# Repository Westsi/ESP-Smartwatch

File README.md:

# ESP32 Based Smartwatch
A smartwatch with modern features such as notifications and Spotify sync, watch faces that can be customised, a 240x240 round LCD screen, and a companion app connected with a custom BLE profile.

## Features
- Custom BLE Profile allowing for
  - Notification Sync
  - Time Sync
  - Spotify Sync
  - Exercise Sync
- Auto Sleep Timeout to save battery
- Adjustable Brightness
- Semi-customizeable Watch Faces
- Rudimentary Exercise Tracker
- Code for wireless (OTA) updates (most code from [fbiego/ESP32_BLE_OTA_Arduino](https://github.com/fbiego/ESP32_BLE_OTA_Arduino))

## Prototype 1

[Demo Video (youtube.com)](https://www.youtube.com/watch?v=f3tLT5q3JZY)

## TODO
- [ ] Fix OTA updates over BLE
- [ ] Make weather sync as well
- [x] Put it all together
- [ ] Calibrate battery level code
- [ ] Make Exercise Tracker work properly with accelerometer
- [ ] Saveable Preferences

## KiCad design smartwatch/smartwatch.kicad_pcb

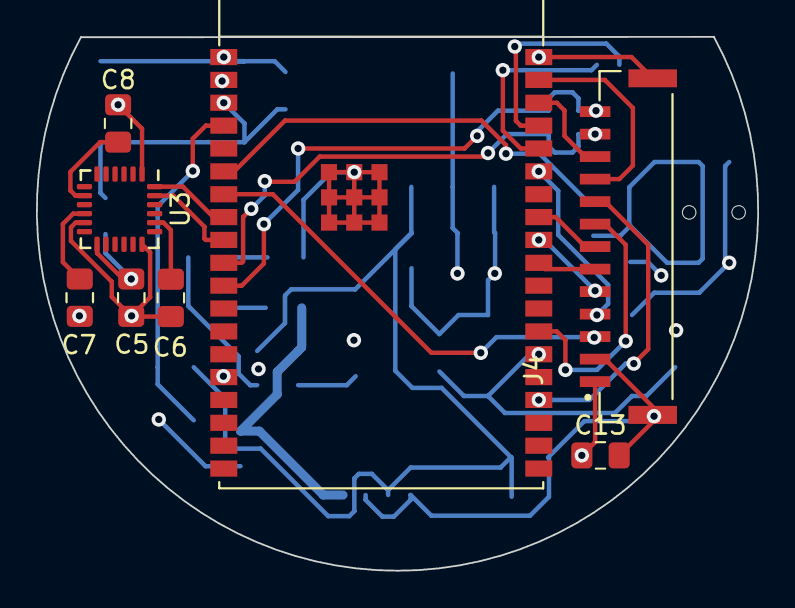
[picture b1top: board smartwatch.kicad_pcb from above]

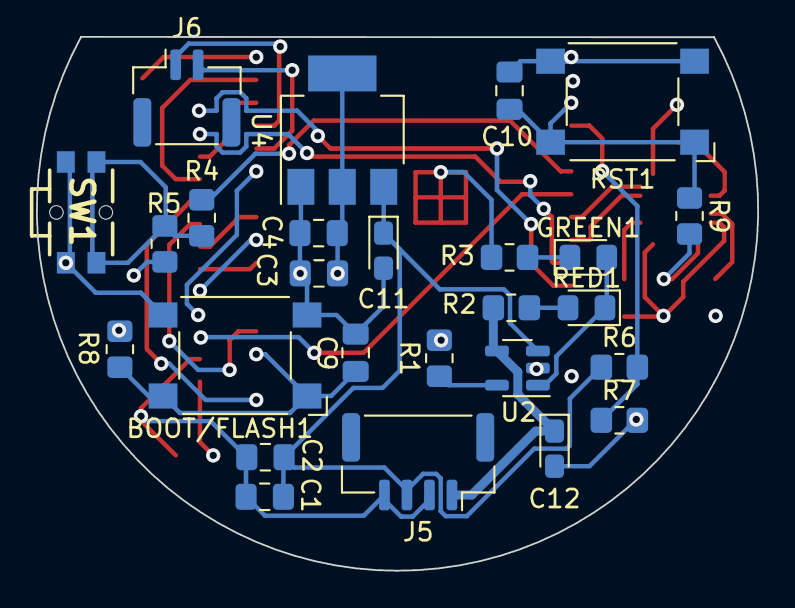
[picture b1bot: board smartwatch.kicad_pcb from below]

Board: 4 copper layers, 40.1 x 29.7 mm, 34 parts (26 on the bottom side), 31 nets.

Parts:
BOOT/FLASH1: BOOT/FLASH; SW_SPST_Omron_B3FS-100xP
C1, C4, C8, C13: 10nF; C_0805_2012Metric_Pad1.18x1.45mm_HandSolder
C2, C3, C9, C10: 100nF; C_0805_2012Metric_Pad1.18x1.45mm_HandSolder
C5, C7: 0.1uF; C_0805_2012Metric_Pad1.18x1.45mm_HandSolder
C6: 2.2nF; C_0805_2012Metric_Pad1.18x1.45mm_HandSolder
C11, C12: Polarized_10uF; CP_EIA-2012-12_Kemet-R_Pad1.30x1.05mm_HandSolder
GREEN1: CHARGED; LED_0805_2012Metric_Pad1.15x1.40mm_HandSolder
J4: SM13B-GHS-TB; JST_SM13B-GHS-TB
J5: BAT_CON/DC_CON; JST_GH_SM04B-GHS-TB_1x04-1MP_P1.25mm_Horizontal
J6: PROG_INT; JST_GH_SM02B-GHS-TB_1x02-1MP_P1.25mm_Horizontal
R1: 2.2KΩ; R_0805_2012Metric_Pad1.20x1.40mm_HandSolder
R2, R3: 470Ω; R_0805_2012Metric_Pad1.20x1.40mm_HandSolder
R4, R5, R6, R7, R8, R9: 10KΩ; R_0805_2012Metric_Pad1.20x1.40mm_HandSolder
RED1: CHARGING; LED_0805_2012Metric_Pad1.15x1.40mm_HandSolder
RST1: RST; SW_SPST_Omron_B3FS-100xP
SW1: SW_Push; Wurth_Elektronik_436331045822
U1: ESP32-WROVER-E
U2: MCP73831-5-OT; SOT-23-5
U3: MPU-6050; InvenSense_QFN-24_4x4mm_P0.5mm
U4: TLV1117-33; SOT-223-3_TabPin2

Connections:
3V3: C3.2, C4.2, C5.1, C13.1, J4.1, R5.2, R8.1, R9.2, U1.2 (3V3), U3.13 (VDD), U4.2 (VO)
BAT_MEASURE: R6.2, R7.1, U1.4 (SENSOR_VP/GPIO36/ADC1_CH0)
BAT_VDD: C1.2, C2.2, C11.1, J5.3, R6.1, U2.3 (V_{BAT}), U4.3 (VI)
BTN_INP: R4.2, U1.6 (GPIO34/ADC1_CH6)
DC_5V_IN: C12.1, J5.1, R2.1, U2.4 (V_{DD})
DC_GND: BOOT/FLASH1.2, C1.1, C2.1, C3.1, C4.1, C5.2, C6.2, C7.2, C8.2, C9.1, C10.1, C11.2, C12.2, C13.2, J4.2, J4.SH1 (SHIELD), J4.SH2 (SHIELD), J5.2, J5.4, R1.2, R3.2, R7.2, RST1.2, SW1.2, U1.1 (GND), U1.15 (GND), U1.38 (GND), U1.39 (GND_THERMAL), U2.2 (V_{SS}), U3.1 (CLKIN), U3.11 (FSYNC), U3.18 (GND), U4.1 (GND)
EN: C10.2, R9.1, RST1.1, U1.3 (EN/CHIP_PU)
IO0: BOOT/FLASH1.1, C9.2, R8.2, U1.25 (GPIO0/BOOT/ADC2_CH1)
MCP_1: GREEN1.2 (A), RED1.1 (K), U2.1 (STAT)
MPU_SCL: U1.9 (32K_XN/GPIO33/ADC1_CH5), U3.23 (SCL)
MPU_SDA: U1.8 (32K_XP/GPIO32/ADC1_CH4), U3.24 (SDA)
MPU_VLOGIC: C8.1, U3.8 (VLOGIC)
unnamed: GREEN1.1 (K), R3.1
unnamed: R4.1, R5.1, SW1.1
unnamed: R2.2, RED1.2 (A)
unnamed: R1.1, U2.5 (PROG)
unnamed: C6.1, U3.20 (CPOUT)
unnamed: C7.1, U3.10 (REGOUT)
RX: J6.2, U1.34 (U0RXD/GPIO3)
SCR_BL: J4.9, U1.23 (MTDO/GPIO15/ADC2_CH3)
SCR_CS: J4.6, U1.29 (GPIO5)
SCR_DC: J4.7, U1.31 (GPIO19)
SCR_MISO: J4.3, U1.7 (GPIO35/ADC1_CH7)
SCR_MOSI: J4.4, U1.33 (GPIO21)
SCR_RST: J4.8, U1.26 (ADC2_CH0/GPIO4)
SCR_SCLK: J4.5, U1.30 (GPIO18)
TOUCH_IRQ: J4.12, U1.10 (DAC_1/ADC2_CH8/GPIO25)
TOUCH_RST: J4.13, U1.11 (DAC_2/ADC2_CH9/GPIO26)
TOUCH_SCL: J4.11, U1.36 (GPIO22)
TOUCH_SDA: J4.10, U1.37 (GPIO23)
TX: J6.1, U1.35 (U0TXD/GPIO1)

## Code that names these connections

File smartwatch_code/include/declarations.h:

#ifndef DECLARATIONS_H_
#define DECLARATIONS_H_

#define SCREEN_W 240
#define SCREEN_H 240

#define MPU_SDA 32
#define MPU_SCL 33

#define CASE_BUTTON 34

#define BATTERY_MEASURE 36


#define SCREEN_MISO 35
#define SCREEN_MOSI 21
#define SCREEN_CLK 18
#define SCREEN_CS 5
#define SCREEN_DC 19
#define SCREEN_RST 4
#define SCREEN_BL 15

#define TOUCH_SDA 23
#define TOUCH_SCL 22
#define TOUCH_IRQ 25
#define TOUCH_RST 26

#define MANU_NAME "XONIZE_IND"
#define MODEL_NUM "XSW1"
#define FIRMWARE_REV "0.2.0-alpha.1"
#define SOFTWARE_REV "0.4.1-alpha.1"
#define HARDWARE_REV "1.0.0-beta.1"
#define SYSTEM_ID "XSW-DEADBEEF1"

#define TFT_XON_BLUE 0x3535 // #37a4ad
#define TFT_XON_DARK_BLUE 0x3cf4 // #379da8
#define TFT_SPOT_GREEN 0x25ca // #1db954
// https://rgbcolorpicker.com/565


#endif

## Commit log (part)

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2024-03-30 finished pcb and sch
2024-03-31 added button
2024-04-06 code and some updates
2024-04-07 updated phone connection
2024-04-15 ble works inc appearance and command channel
2024-04-16 started phone connect app
2024-04-17 app works basic
2024-04-17 app works
2024-04-20 added notification stuff
2024-04-20 notifications work!
2024-04-23 couple fixes
2024-05-01 cannot get spotify data, notifications broken
2024-05-04 fixed spotify and notification problems
2024-05-08 updated xml file
2024-05-08 added platformio libdeps to git because TFT_eSPI needs User_Setup file
2024-05-08 updated user_setup
2024-05-08 changed screen and added font
2024-05-08 updated planning comments in touchscreen
2024-05-09 homescreen iffy, custom font not working :/
2024-05-10 created all fonts
2024-05-10 fixed naming of Light 12 and 14 fonts
2024-05-10 shows time now
2024-05-10 updated pcb schematic and design
2024-05-11 time syncing from phone works
2024-05-12 interaction handlers work, probably can be made more efficient at checking
2024-05-15 attempted to make analogue clock
2024-05-15 asdfgh
2024-05-15 clock works!
2024-05-16 UNTESTED added notification receiving code
2024-05-17 sending and receiving notifications works!
2024-05-17 removed unnecessary print statements
2024-05-17 moved files, created notification screen
2024-05-17 changes and started notif rendering
2024-05-18 notifications work
2024-05-18 fixed naming conflict
2024-05-18 fixed animate function
2024-05-19 animations
2024-05-20 added non animated switch
2024-05-23 added more fonts and digital watch face
2024-05-23 changed digital watch face
2024-05-23 added template screen
2024-05-24 started exercise screen
2024-05-25 exercise arc
2024-06-03 sleep and awake works
2024-06-03 changed schematic and pcb of push button connection
2024-06-03 backlight toggling, stepcount ring
2024-06-03 created todo.txt
2024-06-04 found images for icons
2024-06-04 renamed images and generated 160 versions
2024-06-04 moved images
2024-06-04 made actual 160x160 icons
2024-06-04 actually good images
2024-06-04 all images and icons done
2024-06-04 recolouring works
2024-06-06 generated gerbers for pcb
2024-06-06 updated todo
2024-06-09 fully redesigned board - ground and power planes :)
2024-06-12 started settings
2024-06-13 slider done
2024-06-15 stuff
2024-06-21 saving and loading brightness works
2024-07-22 Create LICENSE
2024-08-02 implemented battery reading in both code and schem
2024-08-02 updated batt values
2024-08-03 battery percentage calculations seem to work
2024-08-03 added todo
2024-08-04 made some changes to sleep
2024-08-05 made icons stored in static memory
2024-08-05 homescreen ui works
2024-08-06 kicad
2024-08-06 syncs spotify data successfully, doesnt display yet
2024-08-07 one way spotify shit and fixed time zones
2024-08-07 playback controls work!
2024-08-07 spotify works (mostly) . app crashes periodically idk why
2024-08-07 added watchface toggle to settings
2024-08-08 updated todo section of readme
2024-08-08 added saving for watchface
2024-08-09 fixed pcb layout to ensure that wireless module hangs off board
2025-01-27 updated gerbers and sent for manufacture
2025-01-27 enabled DMA? messing around with animations.
2025-04-06 added missing pullups
2025-04-12 fixed crash and updated gradle
2025-04-12 updater written, seems to compile properly. have to write app before I can test
2025-04-13 hell of a lot of app shit. fuck me i hate kotlin
2025-04-14 who even knows anymore
2025-04-15 i give it a 20% chance of eventually working. the fucking thing writes it 4 times and ITS SO SLOWWWW
2025-04-19 might have fixed it idk i dont wanna test it out
2025-05-18 added connector
2025-05-19 finished routing
2025-05-30 added a blackjack game - untested on hardware
2025-05-31 added functionality for getting blackjacks
2025-07-12 fixed errors
2025-08-15 added connectors for all and reroute
2026-03-28 regenerated for prod
